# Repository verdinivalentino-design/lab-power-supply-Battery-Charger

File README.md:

# ⚡​Car Battery Charger + Power Supply🔋​🚗​​
> `ATX PC Supply transformed in a bench supply + car battery charger`

## 📄[Documentation](./documentation) (Hack Club requirements)
Here you will find the main resources and documentation of the project.

#### [⚡📐CAD Case & Electronics design](./documentation/cad)
#### [​📄🧠​Research Fundamentation](./documentation/research)
#### [📋💲Budget BOM (Bill of materials)](./documentation/budget)

##

### [🧪​🔨​ Demo & prototypes testing](./documentation/research)

## Who's behind & Why

Hello! I am Valentino, an Argentine Electromechanics Technician Student, enthusiastic about Physics and Science. Since this year started I had the idea of recycling an old PC ATX Power supply and build a Lab Supply and a battery charger, because thid devices can hold more than 30 Ampers of current (which is a lot). Now, Holydays started and along this repo you will see all my research from fundamentation of  regulable electronics to my CAD designs.

#

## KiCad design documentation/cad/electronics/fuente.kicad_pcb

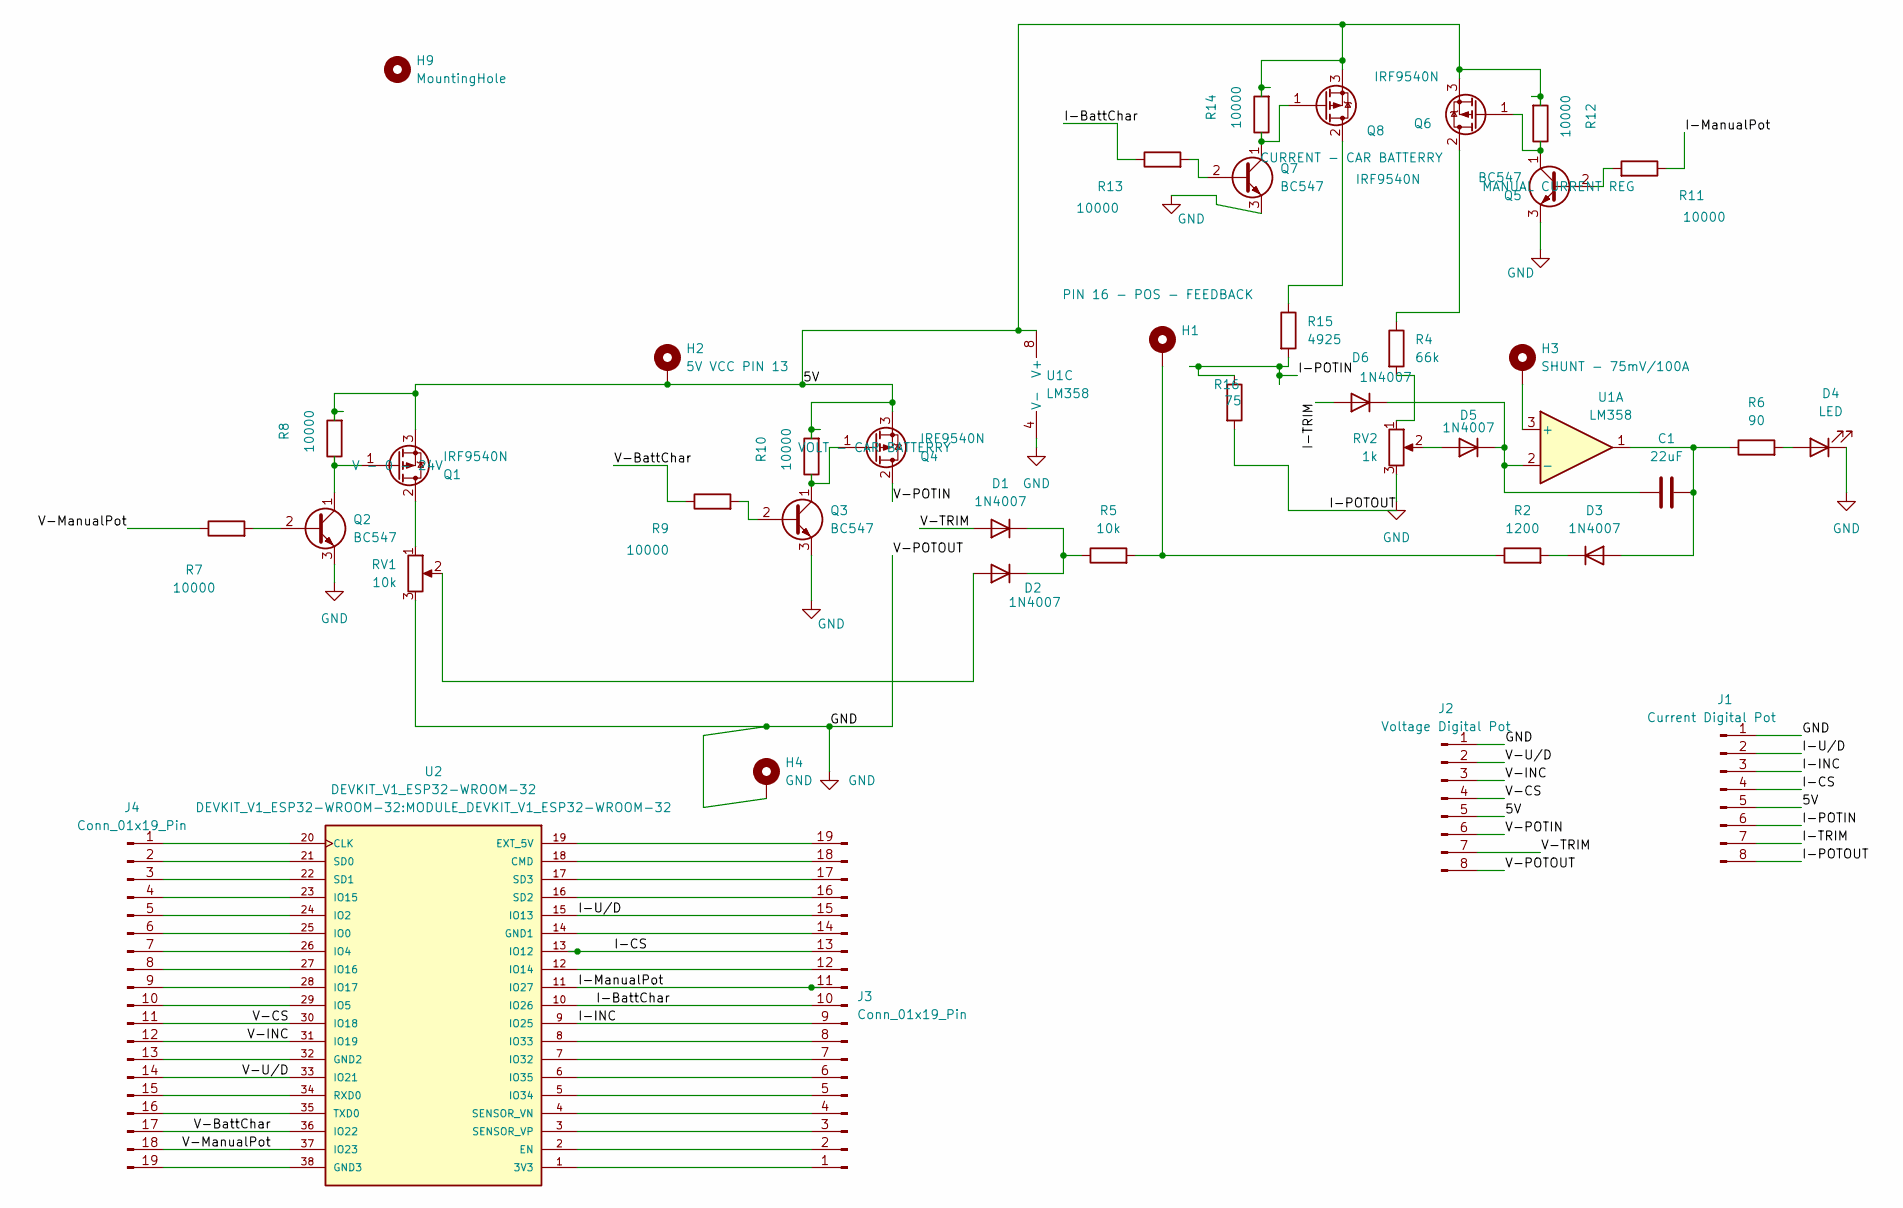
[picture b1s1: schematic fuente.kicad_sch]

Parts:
C1: 22uF; C_Disc_D5.0mm_W2.5mm_P2.50mm
D1, D2, D3, D5, D6: 1N4007; D_DO-41_SOD81_P10.16mm_Horizontal
D4: LED; LED_D5.0mm
H1: PIN 16 - POS - FEEDBACK; SolderWire-1.5sqmm_1x01_D1.7mm_OD3.9mm
H2: SolderWire-1.5sqmm_1x01_D1.7mm_OD3.9mm
H3: SHUNT - 75mV/100A; SolderWire-1.5sqmm_1x01_D1.7mm_OD3.9mm
H4: GND; SolderWire-1.5sqmm_1x01_D1.7mm_OD3.9mm
H9: MountingHole; MountingHole_3.2mm_M3_DIN965_Pad_TopBottom
J1: Current Digital Pot; X9c103s_DigitalPot_10k
J2: Voltage Digital Pot; X9c103s_DigitalPot_10k
J3, J4: Conn_01x19_Pin; PinHeader_1x19_P2.54mm_Vertical
Q1, Q4, Q6, Q8: IRF9540N; TO-220-3_Vertical
Q2, Q3, Q5, Q7: BC547; TO-92_Inline
R2: 1200; R_Box_L8.4mm_W2.5mm_P5.08mm
R4: 66k; R_Axial_DIN0207_L6.3mm_D2.5mm_P7.62mm_Horizontal
R5: 10k; R_Axial_DIN0207_L6.3mm_D2.5mm_P7.62mm_Horizontal
R6: 90; R_Axial_DIN0207_L6.3mm_D2.5mm_P7.62mm_Horizontal
R7, R8, R9, R10, R11, R12, R13, R14: 10000; R_Axial_DIN0207_L6.3mm_D2.5mm_P7.62mm_Horizontal
R15: 4925; R_Axial_DIN0207_L6.3mm_D2.5mm_P7.62mm_Horizontal
R16: 75; R_Axial_DIN0207_L6.3mm_D2.5mm_P7.62mm_Horizontal
RV1: 10k; Potentiometer_ACP_CA14-H2,5_Horizontal
RV2: 1k; Potentiometer_ACP_CA14-H2,5_Horizontal
U1: LM358; DIP-8_W7.62mm
U2: DEVKIT_V1_ESP32-WROOM-32; MODULE_DEVKIT_V1_ESP32-WROOM-32; MPN DEVKIT V1 ESP32-WROOM-32

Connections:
/5V: H2.1 (1_1), J1.5, J2.5, Q1.3 (S), Q4.3 (S), Q6.3 (S), Q8.3 (S), R8.2, R10.2, R12.2, R14.2, U1.8 (V+)
/I-BattChar: J3.10, R13.1, U2.10 (IO26)
/I-CS: J1.4, J3.13, U2.13 (IO12)
/I-INC: J1.3, J3.9, U2.9 (IO25)
/I-ManualPot: J3.11, R11.1, U2.11 (IO27)
/I-POTIN: J1.6, R15.2, R16.1
/I-POTOUT: J1.8, R16.2
/I-TRIM: D6.2 (A), J1.7
/I-U/D: J1.2, J3.15, U2.15 (IO13)
/V-BattChar: J4.17, R9.1, U2.36 (IO22)
/V-CS: J2.4, J4.11, U2.30 (IO18)
/V-INC: J2.3, J4.12, U2.31 (IO19)
/V-ManualPot: J4.18, R7.1, U2.37 (IO23)
/V-POTIN: J2.6, Q4.2 (D)
/V-TRIM: D1.2 (A), J2.7
/V-U/D: J2.2, J4.14, U2.33 (IO21)
GND: D4.1 (K), H4.1 (1_1), J1.1, J2.1, J2.8, Q2.3 (E), Q3.3 (E), Q5.3 (E), Q7.3 (E), RV1.3, RV2.3, U1.4 (V-)
unnamed: D1.1 (K), D2.1 (K), R5.1
unnamed: D2.2 (A), RV1.2
unnamed: C1.2, D3.2 (A), R6.1, U1.1
unnamed: D3.1 (K), R2.2
unnamed: D4.2 (A), R6.2
unnamed: D5.2 (A), RV2.2
unnamed: C1.1, D5.1 (K), D6.1 (K), U1.2 (-)
unnamed: H1.1 (1_1), R2.1, R5.2
unnamed: J3.1, U2.1 (3V3)
unnamed: J3.2, U2.2 (EN)
unnamed: J3.3, U2.3 (SENSOR_VP)
unnamed: J3.4, U2.4 (SENSOR_VN)
unnamed: J3.5, U2.5 (IO34)
unnamed: J3.6, U2.6 (IO35)
unnamed: J3.7, U2.7 (IO32)
unnamed: J3.8, U2.8 (IO33)
unnamed: J3.12, U2.12 (IO14)
unnamed: J3.14, U2.14 (GND1)
unnamed: J3.16, U2.16 (SD2)
unnamed: J3.17, U2.17 (SD3)
unnamed: J3.18, U2.18 (CMD)
unnamed: J3.19, U2.19 (EXT_5V)
unnamed: J4.1, U2.20 (CLK)
unnamed: J4.2, U2.21 (SD0)
unnamed: J4.3, U2.22 (SD1)
unnamed: J4.4, U2.23 (IO15)
unnamed: J4.5, U2.24 (IO2)
unnamed: J4.6, U2.25 (IO0)
unnamed: J4.7, U2.26 (IO4)
unnamed: J4.8, U2.27 (IO16)
unnamed: J4.9, U2.28 (IO17)
unnamed: J4.10, U2.29 (IO5)
unnamed: J4.13, U2.32 (GND2)
unnamed: J4.15, U2.34 (RXD0)
unnamed: J4.16, U2.35 (TXD0)
unnamed: J4.19, U2.38 (GND3)
unnamed: Q1.2 (D), RV1.1
unnamed: Q1.1 (G), Q2.1 (C), R8.1
unnamed: Q2.2 (B), R7.2
unnamed: Q3.2 (B), R9.2
unnamed: Q3.1 (C), Q4.1 (G), R10.1
unnamed: Q5.2 (B), R11.2
unnamed: Q5.1 (C), Q6.1 (G), R12.1
unnamed: Q6.2 (D), R4.1
unnamed: Q7.2 (B), R13.2
unnamed: Q7.1 (C), Q8.1 (G), R14.1
unnamed: Q8.2 (D), R15.1
unnamed: R4.2, RV2.1
unnamed: H3.1 (1_1), U1.3 (+)

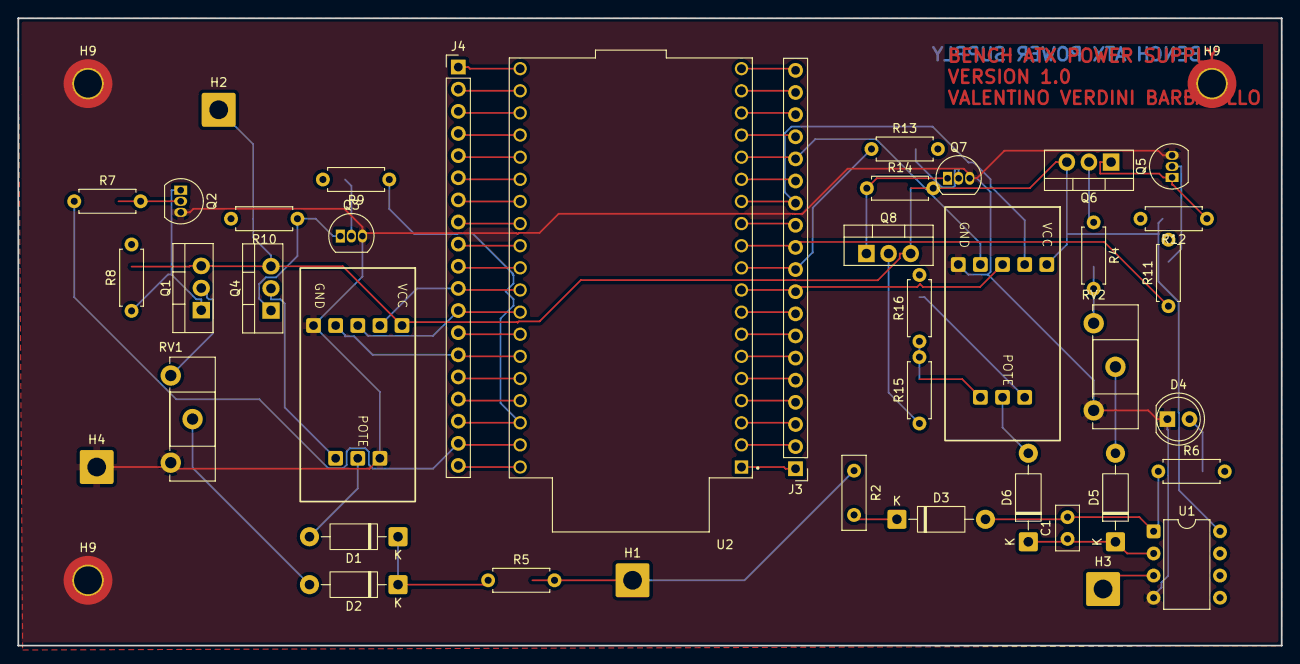
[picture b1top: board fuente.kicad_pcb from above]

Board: 2 copper layers, 145.0 x 72.0 mm, 44 parts (0 on the bottom side), 66 nets.

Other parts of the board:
H9#2, H9#3: MountingHole; MountingHole_3.2mm_M3_DIN965_Pad_TopBottom
